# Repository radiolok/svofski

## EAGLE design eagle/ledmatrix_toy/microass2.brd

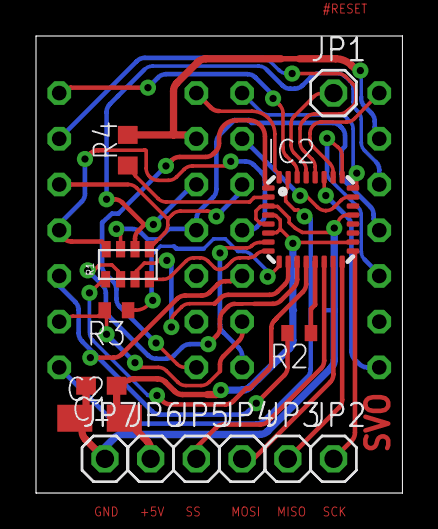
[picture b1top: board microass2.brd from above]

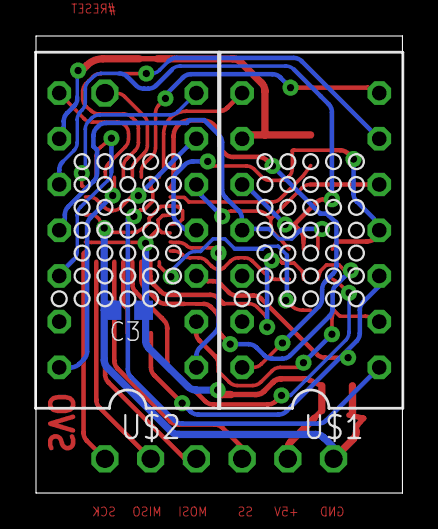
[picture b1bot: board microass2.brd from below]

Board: 2 copper layers, 20.4 x 25.4 mm, 17 parts (3 on the bottom side), 32 nets.

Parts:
C1: C0603
C2: A/3216-18R
C3: C0603K
IC2: MEGA8-MI; MLF32
JP1, JP2, JP3, JP4, JP5, JP6, JP7: 1X01
R1: RESSMD-YC16
R2, R3: R0402
R4: R0603
U$1, U$2: ALS363; ALS-DIL14

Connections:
+5V: C1.1, C2.+, C3.1, IC2.4, IC2.6, IC2.18, JP6.1
BUSA0: IC2.23, U$2.6
BUSA1: IC2.24, U$2.7
BUSA2: IC2.7, U$2.1
BUSA3: IC2.26, U$2.8
BUSA4: IC2.27, U$2.14
BUSA5: IC2.28, U$1.6
BUSA6: IC2.30, U$1.7
BUSA7: IC2.31, U$1.1
BUSA8: IC2.32, U$1.8
BUSA9: IC2.1, U$1.14
BUSC0: R4.2, U$1.9, U$2.9
BUSC1: R1.R4$2, U$1.5, U$2.5
BUSC2: R1.R3$2, U$1.10, U$2.10
BUSC3: R1.R2$2, U$1.11, U$2.11
BUSC4: R1.R1$2, U$1.4, U$2.4
BUSC5: R2.2, U$1.3, U$2.3
BUSC6: R3.2, U$1.2, U$2.2
GND: C1.2, C2.-, C3.2, IC2.3, IC2.5, IC2.21, JP7.1
MISO: IC2.16, JP3.1
MOSI: IC2.15, JP4.1
unnamed: IC2.25, U$2.12
unnamed: IC2.10, R1.R3$1
unnamed: IC2.11, R1.R2$1
unnamed: IC2.12, R1.R1$1
unnamed: IC2.13, R2.1
unnamed: IC2.9, R3.1
unnamed: IC2.2, R4.1
unnamed: IC2.8, R1.R4$1
RESET: IC2.29, JP1.1
SCK: IC2.17, JP2.1
SS: IC2.14, JP5.1

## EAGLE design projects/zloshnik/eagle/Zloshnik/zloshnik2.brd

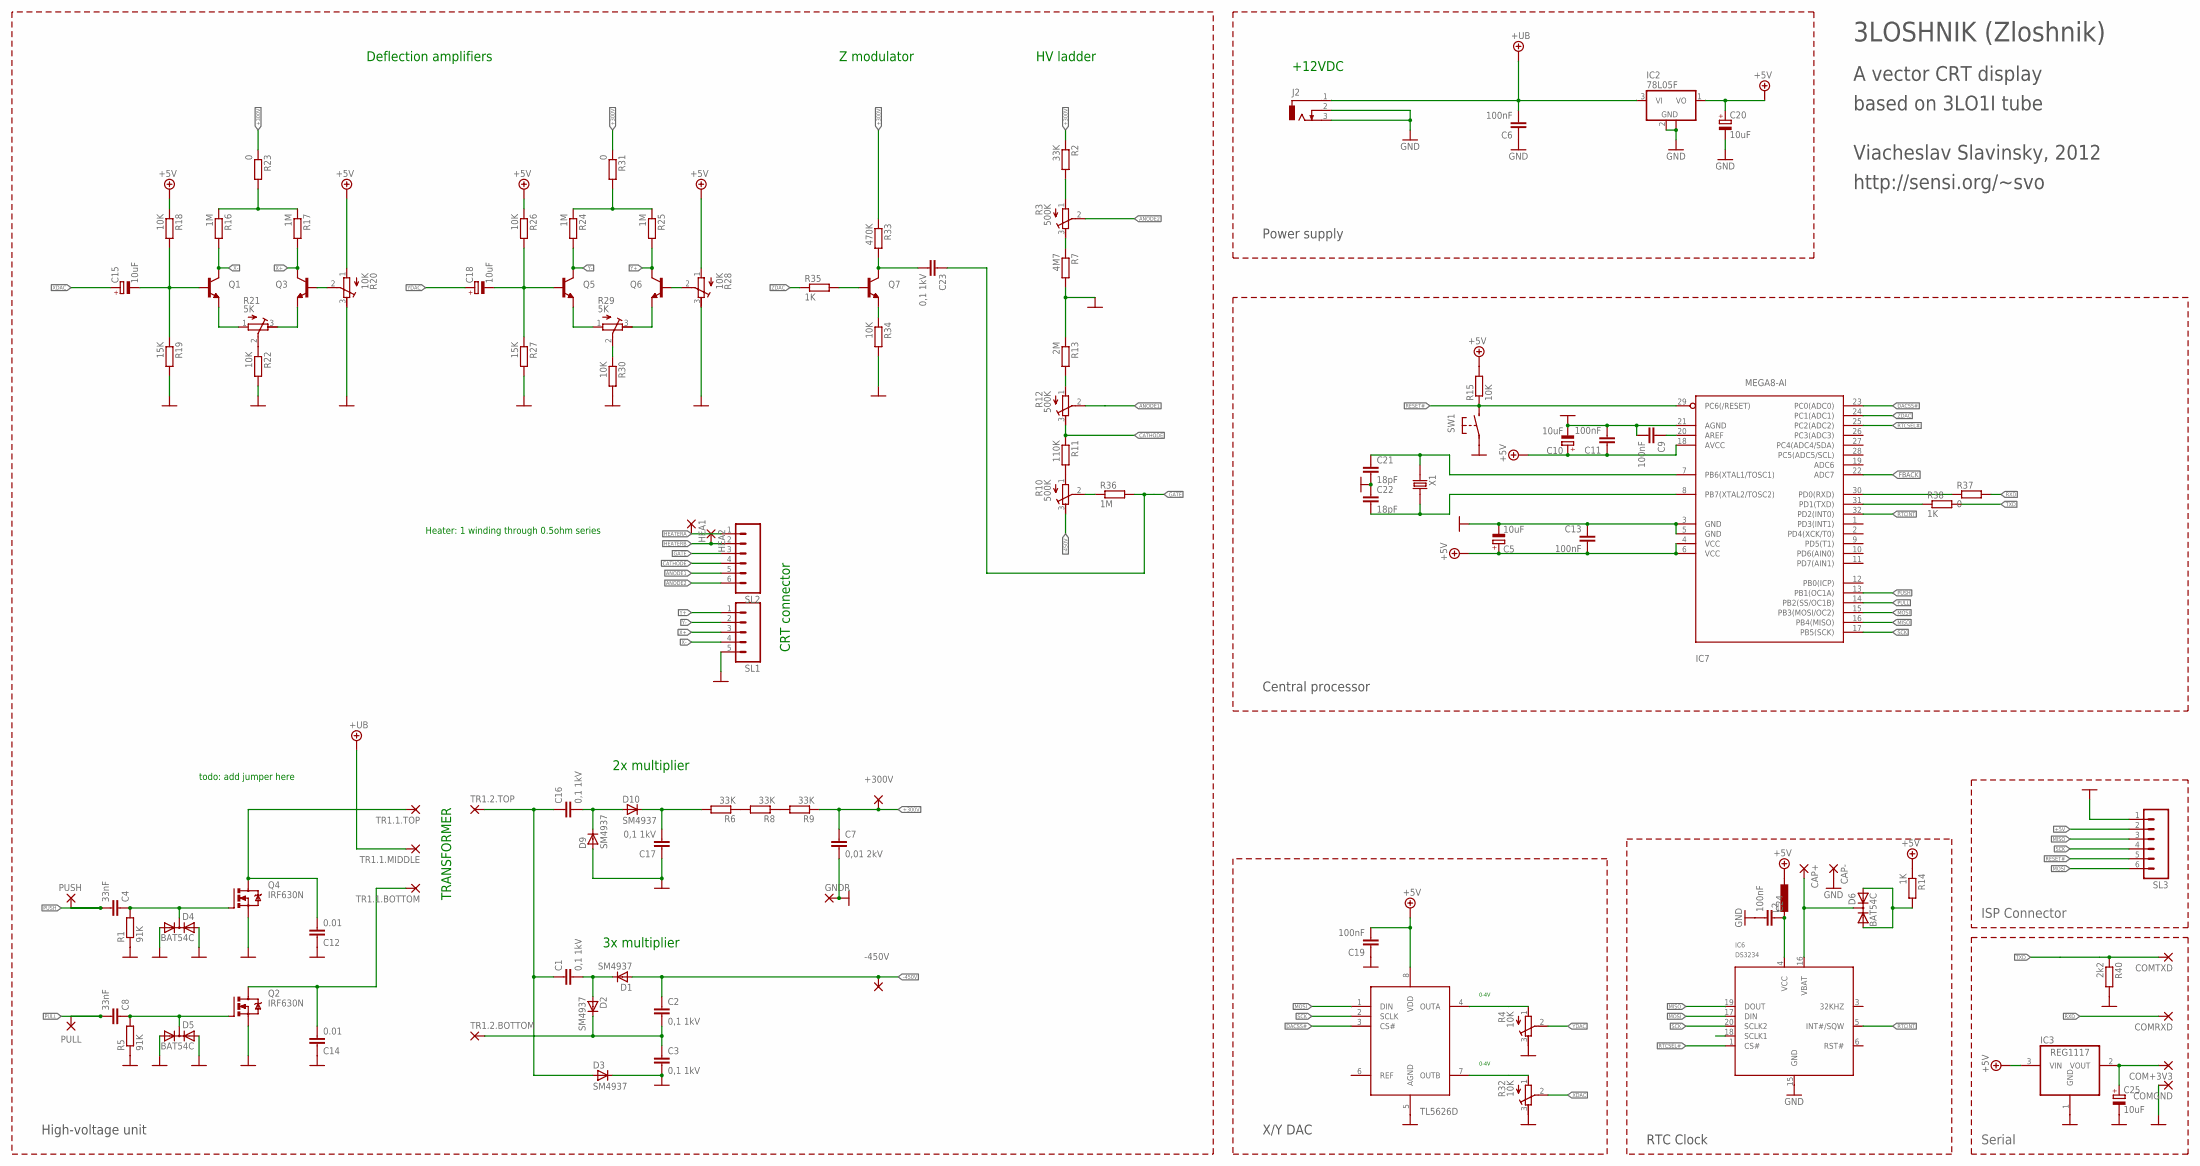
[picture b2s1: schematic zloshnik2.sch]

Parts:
+300V: 1,6/0,8
-450V: 1,6/0,8
C1, C2, C3, C16, C17, C23: 0,1 1kV; C2220K
C4, C8: 33nF; C0805S
C5, C10, C15, C18, C20, C25: 10uF; SMC_B
C6, C9, C11, C13, C19, C24: 100nF; C0603K
C7: 0,01 2kV; C1812
C12, C14: 0.01; C0805S
C21, C22: 18pF; C0805S
CAP+: 2,54/0,8
CAP-: 2,54/0,8
COM+3V3: 1,6/0,8
COMGND: 1,6/0,8
COMRXD: 1,6/0,8
COMTXD: 1,6/0,8
D1, D2, D3, D9, D10: SM4937; SOD87
D4, D5, D6: BAT54C; SOT23
GNDR: 1,6/0,8
HEA1, HEA2: 1,6/0,8
IC1: TLV5626D; SO08
IC2: 78L05F; SOT89
IC3: REG1117; SOT223
IC6: DS3234; SO-20DW
IC7: MEGA8-AI; TQFP32-08
J2: DCJ-SMALL
L2: L-EUL3230M; L3230M
PULL: 1,6/0,8
PUSH: 1,6/0,8
Q1, Q3, Q5, Q6, Q7: TRANSISTOR_NPNSOT23-3; SOT23-3
Q2, Q4: IRF630N; TO220BV
R1, R5: 91K; R0805-SVO
R2, R6, R8, R9: 33K; R0805-SVO
R3, R10, R12: 500K; RTRIM4G/J
R4, R20, R28, R32: 10K; RTRIM4G/J
R7: 4M7; R0805-SVO
R11: 110K; R0805-SVO
R13: 2M; R0805-SVO
R14, R35, R38: 1K; R0805-SVO
R15, R18, R22, R26, R30, R34: 10K; R0805-SVO
R16, R17, R24, R25, R36: 1M; R0805-SVO
R19, R27: 15K; R0805-SVO
R21, R29: 5K; RTRIM4G/J
R23, R31, R37: 0; R0805-SVO
R33: 470K; R0805-SVO
R40: 2k2; R0805-SVO
SL1: M05; 05P
SL2, SL3: M06; 06P
SW1: BUTTON-IT_1181; SW_IT1181
TR1.1.BOTTOM, TR1.1.MIDDLE, TR1.1.TOP, TR1.2.BOTTOM, TR1.2.TOP: 1,6/0,8
X1: XTAL0532; XTAL_0532

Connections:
+3V3: C25.+, COM+3V3.1, IC3.2 (VOUT)
+5V: C5.+, C10.+, C11.1, C13.2, C19.2, C20.+, IC1.8 (VDD), IC2.1 (VO), IC3.3 (VIN), IC7.4 (VCC), IC7.6 (VCC), IC7.18 (AVCC), L2.1, R14.1, R15.2, R18.1, R20.1 (E), R26.1, R28.1 (E), SL3.2
+300V: +300V.1, C7.1, R2.1, R9.1, R23.1, R31.1, R33.1
+UB: C6.2, IC2.3 (VI), J2.1, TR1.1.MIDDLE.1
-450V: -450V.1, C2.1, D1.2 (A), R10.3 (A)
AC_A: C1.1, C16.1, D3.2 (A), TR1.2.TOP.1
AC_B: C2.2, C3.1, D2.1 (C), TR1.2.BOTTOM.1
ANODE1: R12.2 (S), SL2.5
ANODE2: R3.2 (S), SL2.6
CATHODE: R11.1, R12.3 (A), SL2.4
DACSS#: IC1.3 (CS#), IC7.23 (PC0(ADC0))
FBACK: IC7.22 (ADC7)
GATE: C23.1, R36.2, SL2.3
GND: C3.2, C5.-, C6.1, C7.2, C9.2, C10.-, C11.2, C12.1, C13.1, C14.1, C17.1, C19.1, C20.-, C21.2, C22.1, C24.2, C25.-, CAP-.1, COMGND.1, D3.1 (C), D4.1 (A1), D4.2 (A2), D5.1 (A1), D5.2 (A2), D9.2 (A), GNDR.1, IC1.5 (AGND), IC2.2 (GND), IC2.2@1 (GND), IC3.1 (GND), IC6.15 (GND), IC7.3 (GND), IC7.5 (GND), IC7.21 (AGND), J2.2, J2.3, Q2.S, Q4.S, R1.1, R4.3 (A), R5.1, R7.2, R13.1, R19.2, R20.3 (A), R22.2, R27.2, R28.3 (A), R30.2, R32.3 (A), R34.2, R40.2, SL1.5, SL3.1, SW1.P$1 (P1)
HEATERA: HEA1.1, SL2.1
HEATERB: HEA2.1, SL2.2
HV+300UNF: C17.2, D10.1 (C), R6.2
HVN$3: C1.2, D1.1 (C), D2.2 (A)
HVN$6: C16.2, D9.1 (C), D10.2 (A)
HVN$17: R21.2 (S), R22.1
HVN$18: Q1.2 (E), R21.1 (E)
HVN$19: Q3.2 (E), R21.3 (A)
HVN$21: R29.2 (S), R30.1
HVN$22: R16.1, R17.1, R23.2
HVN$25: Q5.2 (E), R29.1 (E)
HVN$26: Q6.2 (E), R29.3 (A)
HVN$27: R24.1, R25.1, R31.2
MISO: IC6.19 (DOUT), IC7.16 (PB4(MISO)), SL3.3
MOSI: IC1.1 (DIN), IC6.17 (DIN), IC7.15 (PB3(MOSI/OC2)), SL3.6
unnamed: R2.2, R3.1 (E)
unnamed: C4.1, D4.3 (C), Q4.G, R1.2
unnamed: CAP+.1, D6.3 (C), IC6.16 (VBAT)
unnamed: R3.3 (A), R7.1
unnamed: C8.1, D5.3 (C), Q2.G, R5.2
unnamed: IC7.30 (PD0(RXD)), R37.1
unnamed: R12.1 (E), R13.2
unnamed: D6.1 (A1), D6.2 (A2), R14.2
unnamed: R10.1 (E), R11.2
unnamed: C9.1, IC7.20 (AREF)
unnamed: IC7.31 (PD1(TXD)), R38.1
unnamed: Q3.1 (B), R20.2 (S)
unnamed: C15.-, Q1.1 (B), R18.2, R19.1
unnamed: Q6.1 (B), R28.2 (S)
unnamed: C18.-, Q5.1 (B), R26.2, R27.1
unnamed: C21.1, IC7.7 (PB6(XTAL1/TOSC1)), X1.2 (1)
unnamed: IC1.4 (OUTA), R4.1 (E)
unnamed: IC1.7 (OUTB), R32.1 (E)
unnamed: C22.2, IC7.8 (PB7(XTAL2/TOSC2)), X1.4 (2)
unnamed: C23.2, Q7.3 (C), R33.2
unnamed: Q7.2 (E), R34.1
unnamed: R10.2 (S), R36.1
NVN$9: R8.1, R9.2
NVN$11: R6.1, R8.2
PULL: C8.2, IC7.14 (PB2(SS/OC1B)), PULL.1
PUSH: C4.2, IC7.13 (PB1(OC1A)), PUSH.1
RESET#: IC7.29 (PC6(/RESET)), R15.1, SL3.5, SW1.P$2 (P2)
RTCINT: IC6.5 (INT#/SQW), IC7.32 (PD2(INT0))
RTCSEL#: IC6.1 (CS#), IC7.25 (PC2(ADC2))
RTCVCC: C24.1, IC6.4 (VCC), L2.2
RXD: COMRXD.1, R37.2
SCK: IC1.2 (SCLK), IC6.20 (SCLK2), IC7.17 (PB5(SCK)), SL3.4
SW_LOW_A: C14.2, Q2.D, TR1.1.BOTTOM.1
SW_LOW_B: C12.2, Q4.D, TR1.1.TOP.1
TXD: COMTXD.1, R38.2, R40.1
X+: Q3.3 (C), R17.2, SL1.3
X-: Q1.3 (C), R16.2, SL1.4
XDAC: C15.+, R32.2 (S)
Y+: Q6.3 (C), R25.2, SL1.1
Y-: Q5.3 (C), R24.2, SL1.2
YDAC: C18.+, R4.2 (S)
ZDAC: IC7.24 (PC1(ADC1)), R35.1
ZDACN$36: Q7.1 (B), R35.2

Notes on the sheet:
0-4V
ISP Connector
Serial
RTC Clock
todo: add jumper here
Heater: 1 winding through 0.5ohm series
CRT connector
Deflection amplifiers
TRANSFORMER
2x multiplier
3x multiplier
HV ladder
Z modulator
+12VDC
X/Y DAC
TL5626D
Central processor
Power supply
High-voltage unit
3LOSHNIK (Zloshnik)
A vector CRT display
based on 3LO1I tube
Viacheslav Slavinsky, 2012
http://sensi.org/~svo

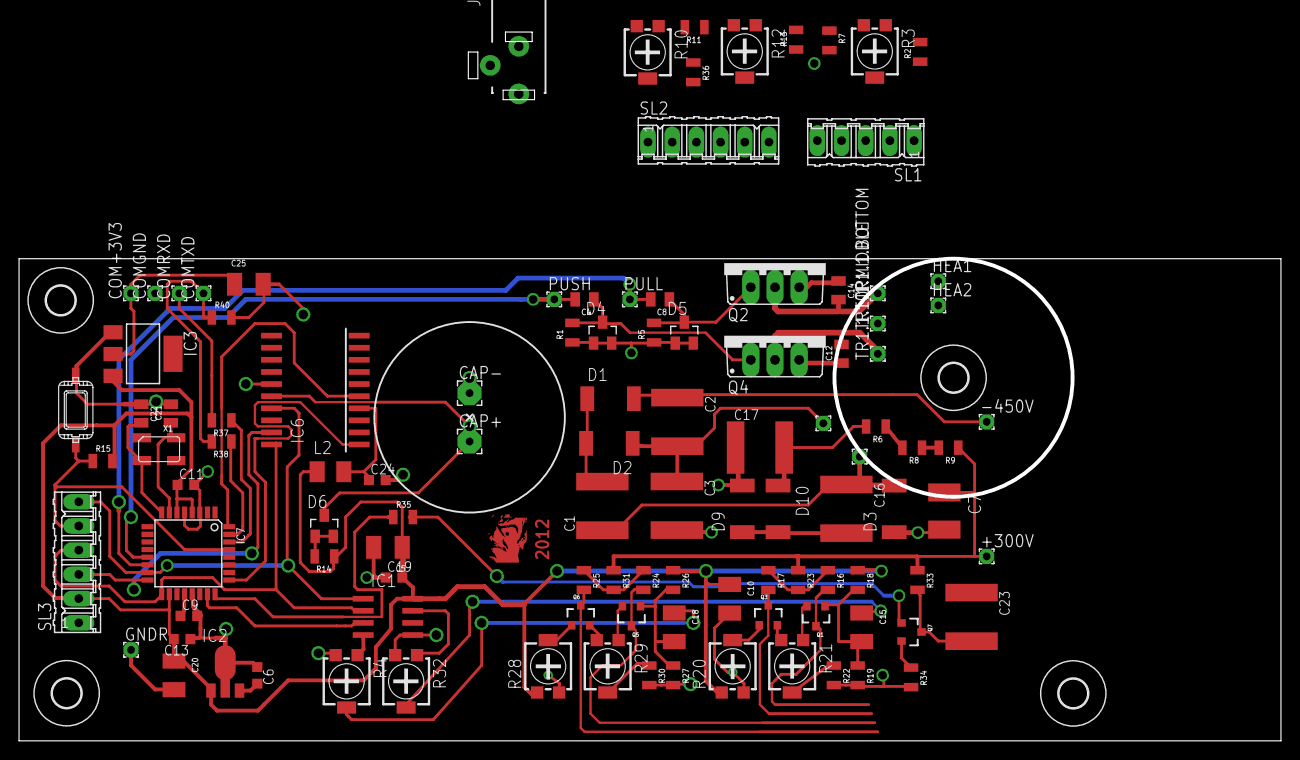
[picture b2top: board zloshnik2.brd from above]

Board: 2 copper layers, 132.5 x 50.6 mm, 113 parts (0 on the bottom side), 71 nets.

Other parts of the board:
U$1, U$2, U$3, U$4: 3,0

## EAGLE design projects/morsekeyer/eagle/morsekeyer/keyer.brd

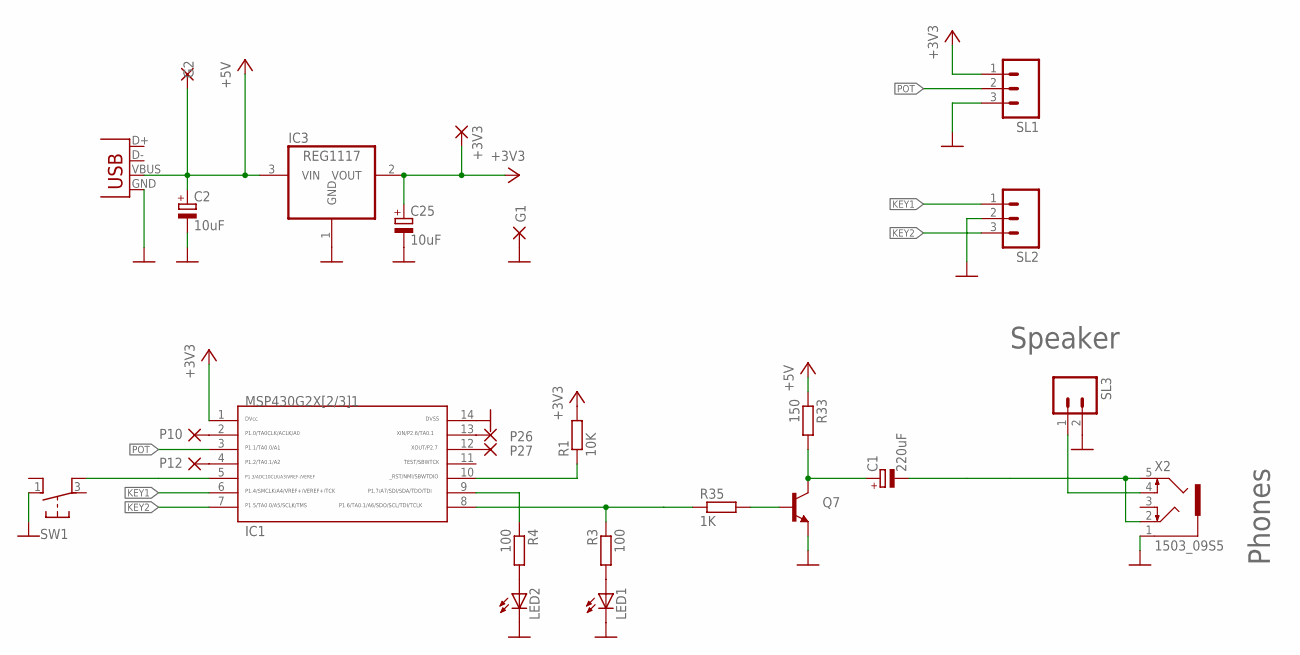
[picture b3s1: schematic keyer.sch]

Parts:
100: R3; R0805-SVO
+3V3: 1,6/0,8
C1: 220uF; D/7343-31R
C2, C25: 10uF; SMC_B
G1, G2: 1,6/0,8
IC1: G2X[2/3]1---N14; N14
IC3: REG1117; SOT223
LED1, LED2: LED3MM
P10, P12, P26, P27: 1,6/0,8
Q7: TRANSISTOR_NPNSOT23-3; SOT23-3
R1: 10K; R0805-SVO
R4: 100; R0805-SVO
R33: 150; R0805-SVO
R35: 1K; R0805-SVO
SL1, SL2: M03; 03P
SL3: M02; 02P
SW1: BUTTON_6X6_THRU; 6X6_BUTTON_THRU
X1: USB-MICROB
X2: 1503_09S5; SYMMETRON5

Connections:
+3V3: +3V3.1, C25.+, IC1.1, IC3.2 (VOUT), R1.2, SL1.1
+5V: C2.+, G2.1, IC3.3 (VIN), R33.1, X1.VBUS
GATE: C1.-, X2.2, X2.5 (3)
GND: C2.-, C25.-, G1.1, IC1.14, IC3.1 (GND), LED1.K (C), LED2.K (C), Q7.2 (E), SL1.3, SL2.2, SL3.2, SW1.1 (P2), X1.GND, X2.1
KEY1: IC1.6, SL2.1
KEY2: IC1.7, SL2.3
MODE1: IC1.5, SW1.4 (P1)
unnamed: IC1.10, R1.1
unnamed: 100.2, LED1.A
unnamed: IC1.2, P10.1
unnamed: LED2.A, R4.2
unnamed: IC1.9, R4.1
unnamed: 100.1, IC1.8, R35.1
unnamed: IC1.4, P12.1
unnamed: IC1.12, P27.1
unnamed: IC1.13, P26.1
unnamed: C1.+, Q7.3 (C), R33.2
unnamed: SL3.1, X2.4 (5)
POT: IC1.3, SL1.2
ZDACN$36: Q7.1 (B), R35.2

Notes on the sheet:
Speaker
Phones

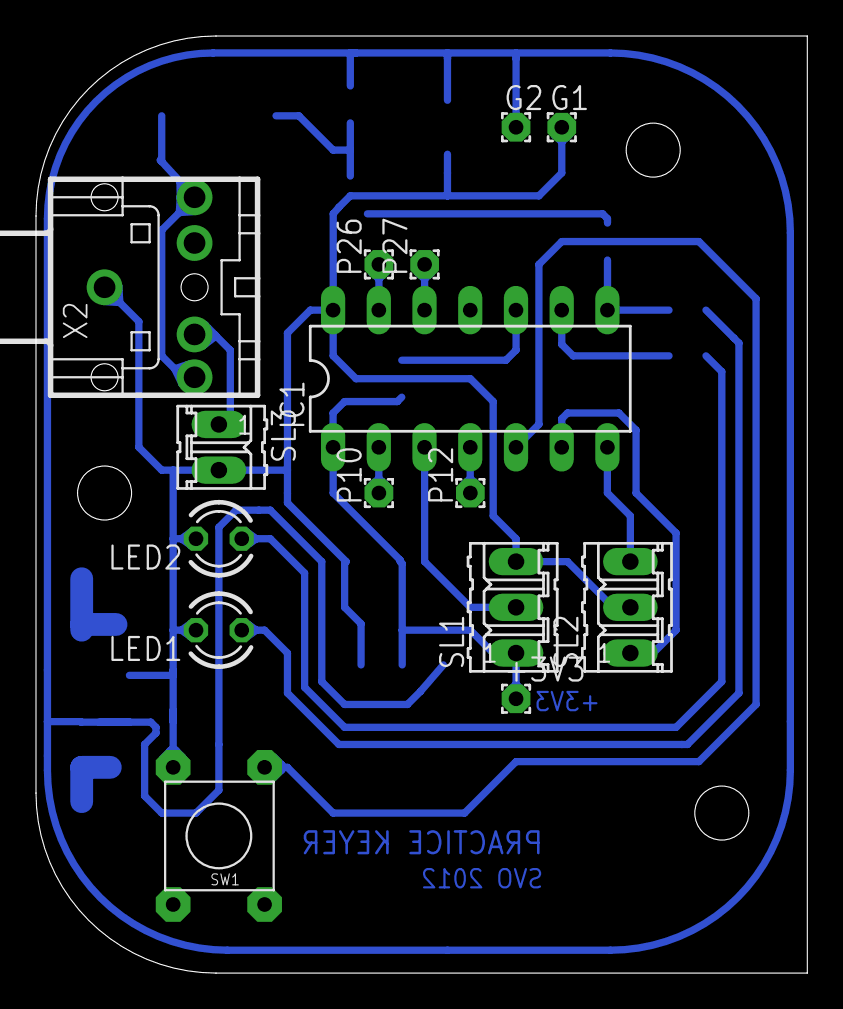
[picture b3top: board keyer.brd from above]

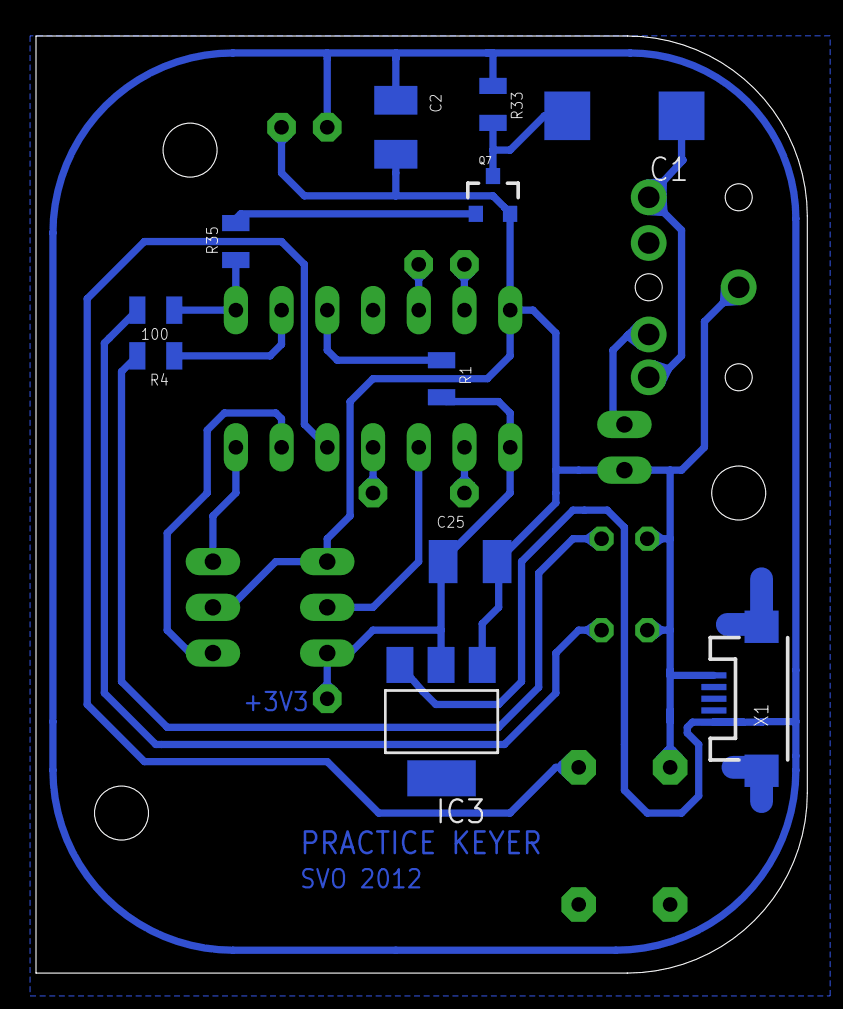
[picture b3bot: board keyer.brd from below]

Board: 2 copper layers, 42.9 x 52.1 mm, 26 parts (11 on the bottom side), 20 nets.

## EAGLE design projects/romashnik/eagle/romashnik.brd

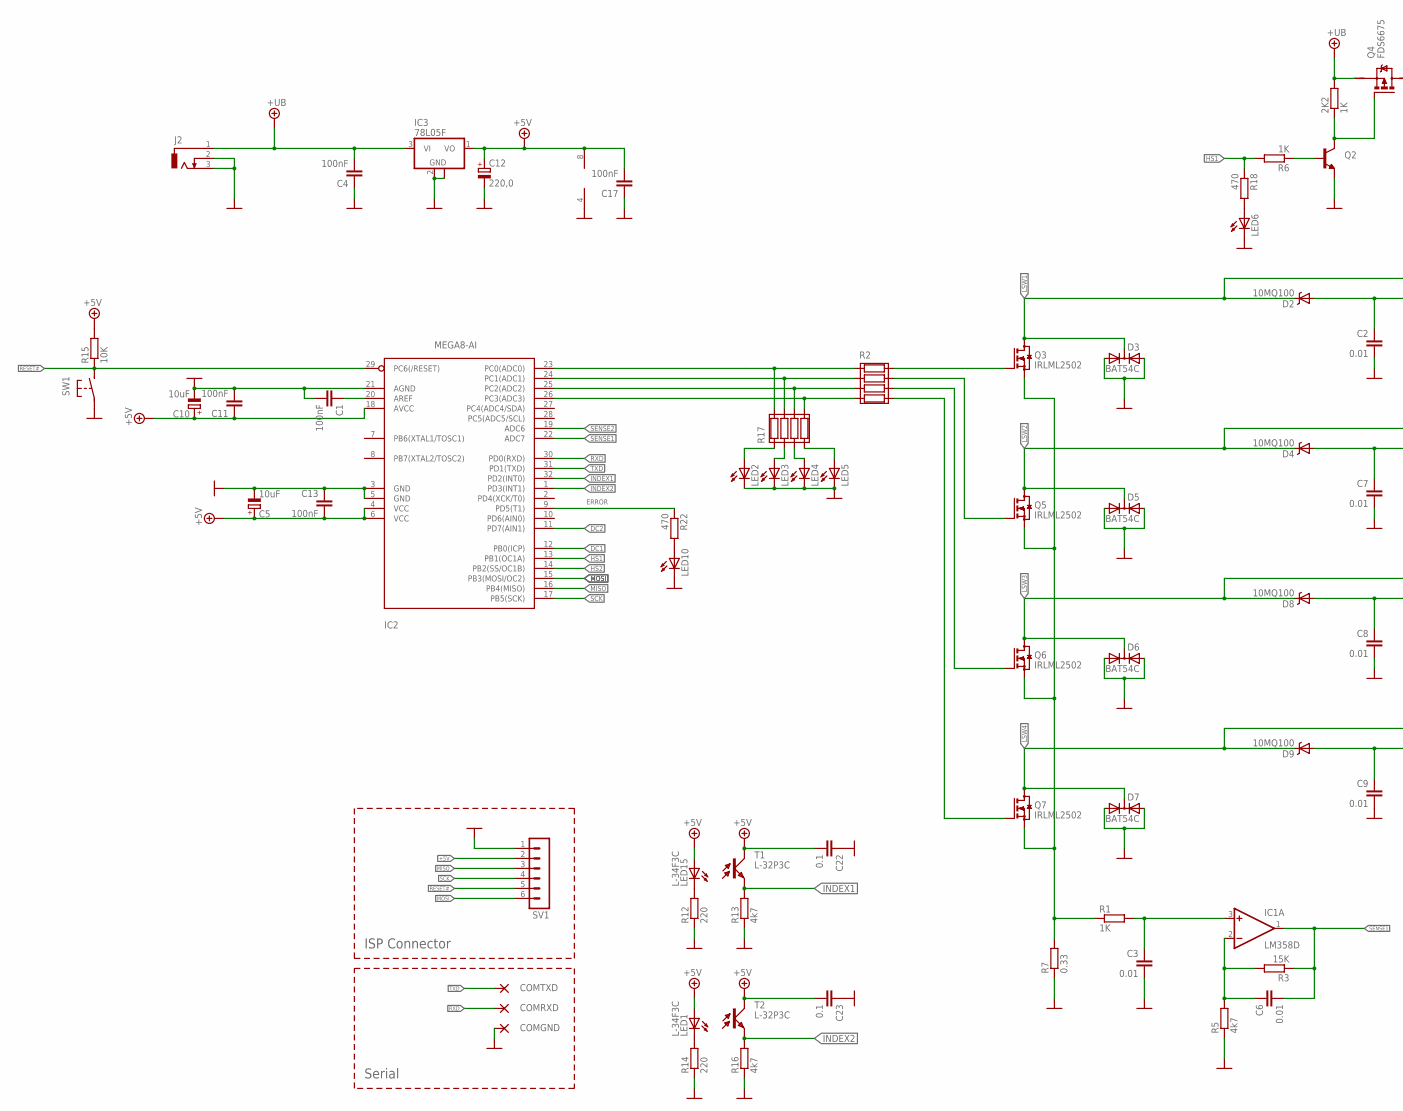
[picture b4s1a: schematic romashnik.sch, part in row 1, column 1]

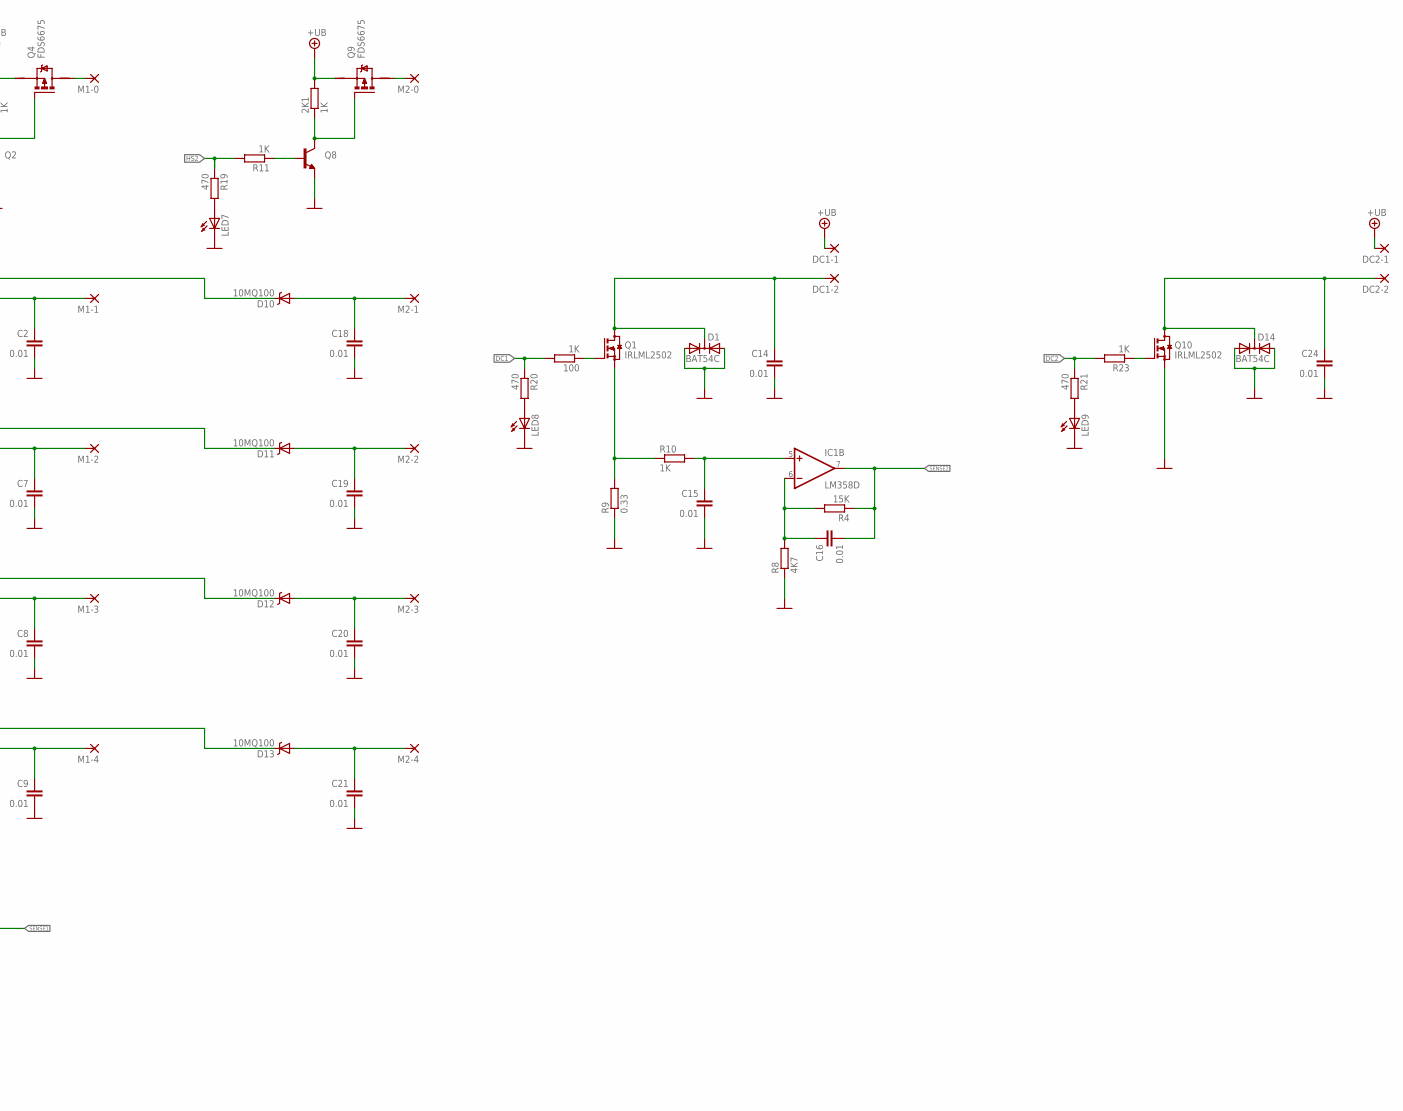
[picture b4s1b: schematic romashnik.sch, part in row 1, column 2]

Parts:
2K1, 2K2, 100: 1K; R0805-SVO
C1, C4, C11, C13, C17: 100nF; C0603K
C2, C3, C6, C7, C8, C9, C14, C15, C16, C18, C19, C20, C21, C24: 0.01; C0603K
C5, C10: 10uF; SMC_B
C12: 220,0; B/3528-21R
C22, C23: 0.1; C0603K
COMGND: 1,6/0,8
COMRXD: 1,6/0,8
COMTXD: 1,6/0,8
D1, D3, D5, D6, D7, D14: BAT54C; SOT23@1
D2, D4, D8, D9, D10, D11, D12, D13: 10MQ100; SMA-DIODE
DC1-1, DC1-2, DC2-1, DC2-2: 1,6/0,8
IC1: LM358D; SO08
IC2: MEGA8-AI; TQFP32-08
IC3: 78L05F; SOT89
J2: DCJ-SMALL
LED1, LED15: L-34F3C; LED3MM
LED2, LED3, LED4, LED5, LED6, LED7, LED8, LED9, LED10: LEDCHIPLED_0603; CHIPLED_0603
M1-0, M1-1, M1-2, M1-3, M1-4, M2-0, M2-1, M2-2, M2-3, M2-4: 1,6/0,8
Q1, Q3, Q5, Q6, Q7, Q10: IRLML2502; SOT23
Q2, Q8: TRANSISTOR_NPNSOT23-3; SOT23-3
Q4, Q9: FDS6675; SO-08
R1, R6, R10, R11, R23: 1K; R0805-SVO
R2, R17: RES4; RESSMD-YC16
R3, R4: 15K; R0805-SVO
R5, R13, R16: 4k7; R0805-SVO
R7, R9: 0.33; R2512
R8: 4K7; R0805-SVO
R12, R14: 220; R0805-SVO
R15: 10K; R0805-SVO
R18, R19, R20, R21, R22: 470; R0805-SVO
SV1: MA06-1
SW1: BUTTON-IT_1181; SW_IT1181
T1, T2: L-32P3C; BPX81

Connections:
+5V: C5.+, C10.+, C11.1, C12.+, C13.2, C17.2, C22.2, C23.2, IC1.8 (V+), IC2.4 (VCC), IC2.6 (VCC), IC2.18 (AVCC), IC3.1 (VO), LED1.A, LED15.A, R15.2, SV1.2, T1.C, T2.C
+UB: 2K1.2, 2K2.2, C4.2, DC1-1.1, DC2-1.1, IC3.3 (VI), J2.1, Q4.1 (S), Q9.1 (S)
DC1: 100.2, IC2.12 (PB0(ICP)), R20.1
DC2: IC2.11 (PD7(AIN1)), R21.1, R23.2
DCMOTEUR1: C14.1, D1.3 (C), DC1-2.1, Q1.3 (D)
DCMOTEUR2: C24.1, D14.3 (C), DC2-2.1, Q10.3 (D)
ERROR: IC2.9 (PD5(T1)), R22.1
GATEQ3: Q3.1 (G), R2.R1$2 (1.2)
GATEQ5: Q5.1 (G), R2.R2$2 (2.2)
GATEQ6: Q6.1 (G), R2.R3$2 (3.2)
GATEQ7: Q7.1 (G), R2.R4$2 (4.2)
GND: C1.2, C2.2, C3.2, C4.1, C5.-, C7.2, C8.2, C9.2, C10.-, C11.2, C12.-, C13.1, C14.2, C15.2, C17.1, C18.2, C19.2, C20.2, C21.2, C22.1, C23.1, C24.2, COMGND.1, D1.1 (A1), D1.2 (A2), D3.1 (A1), D3.2 (A2), D5.1 (A1), D5.2 (A2), D6.1 (A1), D6.2 (A2), D7.1 (A1), D7.2 (A2), D14.1 (A1), D14.2 (A2), IC1.4 (V-), IC2.3 (GND), IC2.5 (GND), IC2.21 (AGND), IC3.2 (GND), IC3.2@1 (GND), J2.2, J2.3, LED2.C, LED3.C, LED4.C, LED5.C, LED6.C, LED7.C, LED8.C, LED9.C, LED10.C, Q2.2 (E), Q8.2 (E), Q10.2 (S), R5.1, R7.1, R8.1, R9.1, R12.1, R13.1, R14.1, R16.1, SV1.1, SW1.P$1 (P1)
HS1: IC2.13 (PB1(OC1A)), R6.2, R18.1
HS2: IC2.14 (PB2(SS/OC1B)), R11.2
HS3: R19.1
INDEX1: IC2.32 (PD2(INT0)), R13.2, T1.E
INDEX2: IC2.1 (PD3(INT1)), R16.2, T2.E
LSW1: D2.C, D3.3 (C), D10.C, Q3.3 (D)
LSW2: D4.C, D5.3 (C), D11.C, Q5.3 (D)
LSW3: D6.3 (C), D8.C, D12.C, Q6.3 (D)
LSW4: D7.3 (C), D9.C, D13.C, Q7.3 (D)
M1: C18.1, D10.A, M2-1.1
M2: C19.1, D11.A, M2-2.1
M3: C20.1, D12.A, M2-3.1
M4: C21.1, D13.A, M2-4.1
M11: C2.1, D2.A, M1-1.1
M12: C7.1, D4.A, M1-2.1
M13: C8.1, D8.A, M1-3.1
M14: C9.1, D9.A, M1-4.1
MISO: IC2.16 (PB4(MISO)), SV1.3
MOSI: IC2.15 (PB3(MOSI/OC2)), SV1.6
unnamed: C3.1, IC1.3 (+IN), R1.2
unnamed: C6.1, IC1.2 (-IN), R3.2, R5.2
unnamed: IC2.23 (PC0(ADC0)), R2.R1$1 (1.1), R17.R1$2 (1.2)
unnamed: IC2.24 (PC1(ADC1)), R2.R2$1 (2.1), R17.R2$2 (2.2)
unnamed: C15.1, IC1.5 (+IN), R10.2
unnamed: IC2.25 (PC2(ADC2)), R2.R3$1 (3.1), R17.R3$2 (3.2)
unnamed: IC2.26 (PC3(ADC3)), R2.R4$1 (4.1), R17.R4$2 (4.2)
unnamed: 100.1, Q1.1 (G)
unnamed: 2K2.1, Q2.3 (C), Q4.4 (G)
unnamed: C1.1, IC2.20 (AREF)
unnamed: Q2.1 (B), R6.1
unnamed: C16.1, IC1.6 (-IN), R4.2, R8.2
unnamed: M1-0.1, Q4.5 (D)
unnamed: LED15.K (C), R12.2
unnamed: LED1.K (C), R14.2
unnamed: LED3.A, R17.R2$1 (2.1)
unnamed: LED4.A, R17.R3$1 (3.1)
unnamed: 2K1.1, Q8.3 (C), Q9.4 (G)
unnamed: Q8.1 (B), R11.1
unnamed: M2-0.1, Q9.5 (D)
unnamed: LED5.A, R17.R4$1 (4.1)
unnamed: LED2.A, R17.R1$1 (1.1)
unnamed: LED7.A, R19.2
unnamed: LED6.A, R18.2
unnamed: LED8.A, R20.2
unnamed: Q10.1 (G), R23.1
unnamed: LED9.A, R21.2
unnamed: LED10.A, R22.2
RESET#: IC2.29 (PC6(/RESET)), R15.1, SV1.5, SW1.P$2 (P2)
RXD: COMRXD.1, IC2.30 (PD0(RXD))
SCK: IC2.17 (PB5(SCK)), SV1.4
SENSE1: C6.2, IC1.1 (OUT), IC2.22 (ADC7), R3.1
SENSE2: C16.2, IC1.7 (OUT), IC2.19 (ADC6), R4.1
SENSEGND: Q3.2 (S), Q5.2 (S), Q6.2 (S), Q7.2 (S), R1.1, R7.2
SENSEGND1: Q1.2 (S), R9.2, R10.1
TXD: COMTXD.1, IC2.31 (PD1(TXD))

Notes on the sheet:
Serial
ISP Connector

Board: 2 copper layers, 110 parts (0 on the bottom side), 66 nets, no tracks yet.

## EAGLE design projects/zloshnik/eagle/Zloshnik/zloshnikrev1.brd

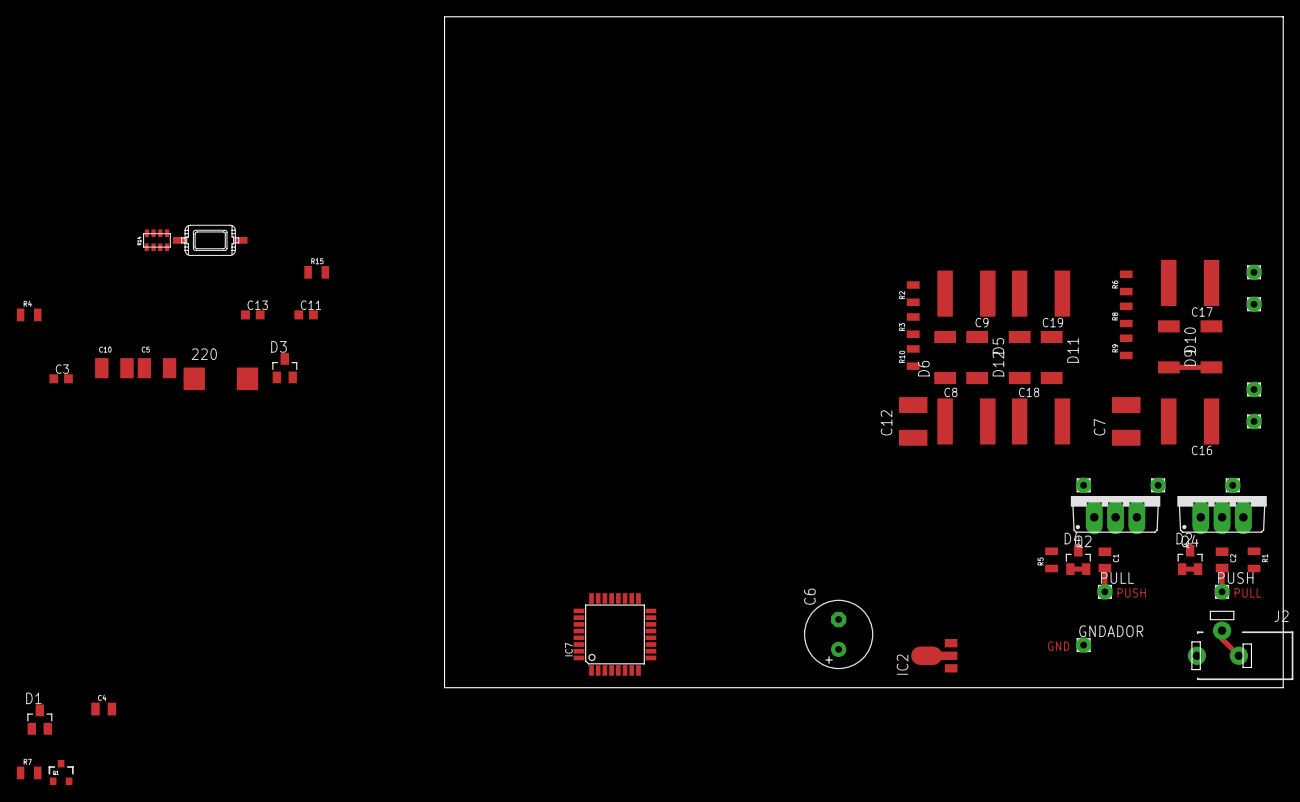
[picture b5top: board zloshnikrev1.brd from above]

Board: 2 copper layers, 100.0 x 80.0 mm, 57 parts (0 on the bottom side), 26 nets.

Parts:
220: D/7343-31R
C1, C2, C4: 33nF; C0805S
C3, C11, C13: 100nF; C0603K
C5, C10: 10uF; SMC_B
C6: 100/24V; E3,5-8
C7, C12: 0,01 2kV; C1812
C8, C9, C16, C17, C18, C19: 0,01 1kV; C2220K
D1, D2, D4: BAT54C; SOT23
D3: BAT54S; SOT23@1
D5, D6, D9, D10, D11, D12: SOD87
GNDADOR: 1,6/0,8
IC2: 78L05F; SOT89
IC7: MEGA8-AI; TQFP32-08
J2: DCJ-SMALL
PULL: 1,6/0,8
PUSH: 1,6/0,8
Q1: IRLML2502; SOT23-3
Q2, Q4: IRF630N; TO220BV
R1, R5, R7: 91K; R0805-SVO
R2, R3, R6, R8, R9, R10: 33K; R0805-SVO
R4: 000; R0805-SVO
R14: RESSMD-YC16
R15: 10K; R0805-SVO
SW1: BUTTON-IT_1181; SW_IT1181
TR1.1.BOTTOM, TR1.1.MIDDLE, TR1.1.TOP, TR1.2.BOTTOM, TR1.2.BOTTOM1, TR1.2.TOP, TR1.2.TOP1: 1,6/0,8

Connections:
+5V: 220.+, C5.+, C10.+, C11.1, C13.2, IC2.1, IC7.4, IC7.6, IC7.18, R15.2
+300V: C7.2, R9.1
+UB: C6.+, IC2.3, J2.1, TR1.1.MIDDLE.1
-600V: C12.2, R10.1
DOT: IC7.1, R4.1, R4.2
GND: 220.-, C3.2, C5.-, C6.-, C7.1, C10.-, C11.2, C12.1, C13.1, C17.1, C19.1, D1.1, D1.2, D2.1, D2.2, D4.1, D4.2, D9.2, D11.1, GNDADOR.1, IC2.2, IC2.2@1, IC7.3, IC7.5, IC7.21, J2.2, J2.3, Q1.2, Q2.S, Q4.S, R1.1, R5.1, R7.1, SW1.P$1, TR1.2.BOTTOM.1, TR1.2.BOTTOM1.1
unnamed: C1.1, D4.3, Q2.G, R5.2
unnamed: Q4.D, TR1.1.TOP.1
unnamed: C2.1, D2.3, Q4.G, R1.2
unnamed: Q2.D, TR1.1.BOTTOM.1
unnamed: C3.1, IC7.20
unnamed: C16.2, D9.1, D10.2
unnamed: C8.2, C18.1, D11.2, D12.1
unnamed: R8.1, R9.2
unnamed: C4.1, D1.3, Q1.1, R7.2
unnamed: R6.1, R8.2
unnamed: R2.1, R3.2
unnamed: C17.2, D10.1, R6.2
unnamed: C8.1, D5.2, D6.1
unnamed: C9.2, D6.2, R2.2
unnamed: C16.1, C18.2, TR1.2.TOP.1, TR1.2.TOP1.1
unnamed: C9.1, C19.2, D5.1, D12.2
unnamed: R3.1, R10.2
PULL: C1.2, IC7.14, PULL.1
PUSH: C2.2, IC7.13, PUSH.1
RESET#: IC7.29, R15.1, SW1.P$2

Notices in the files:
parts and their libraries:
SparkFun: Licensing: CC v3.0 Share-Alike You are welcome to use this library for commercial purposes.
xmaker: Licensing: CC v3.0 Attribution-Share Alike
http://creativecommons.org/licenses/by-sa/3.0
